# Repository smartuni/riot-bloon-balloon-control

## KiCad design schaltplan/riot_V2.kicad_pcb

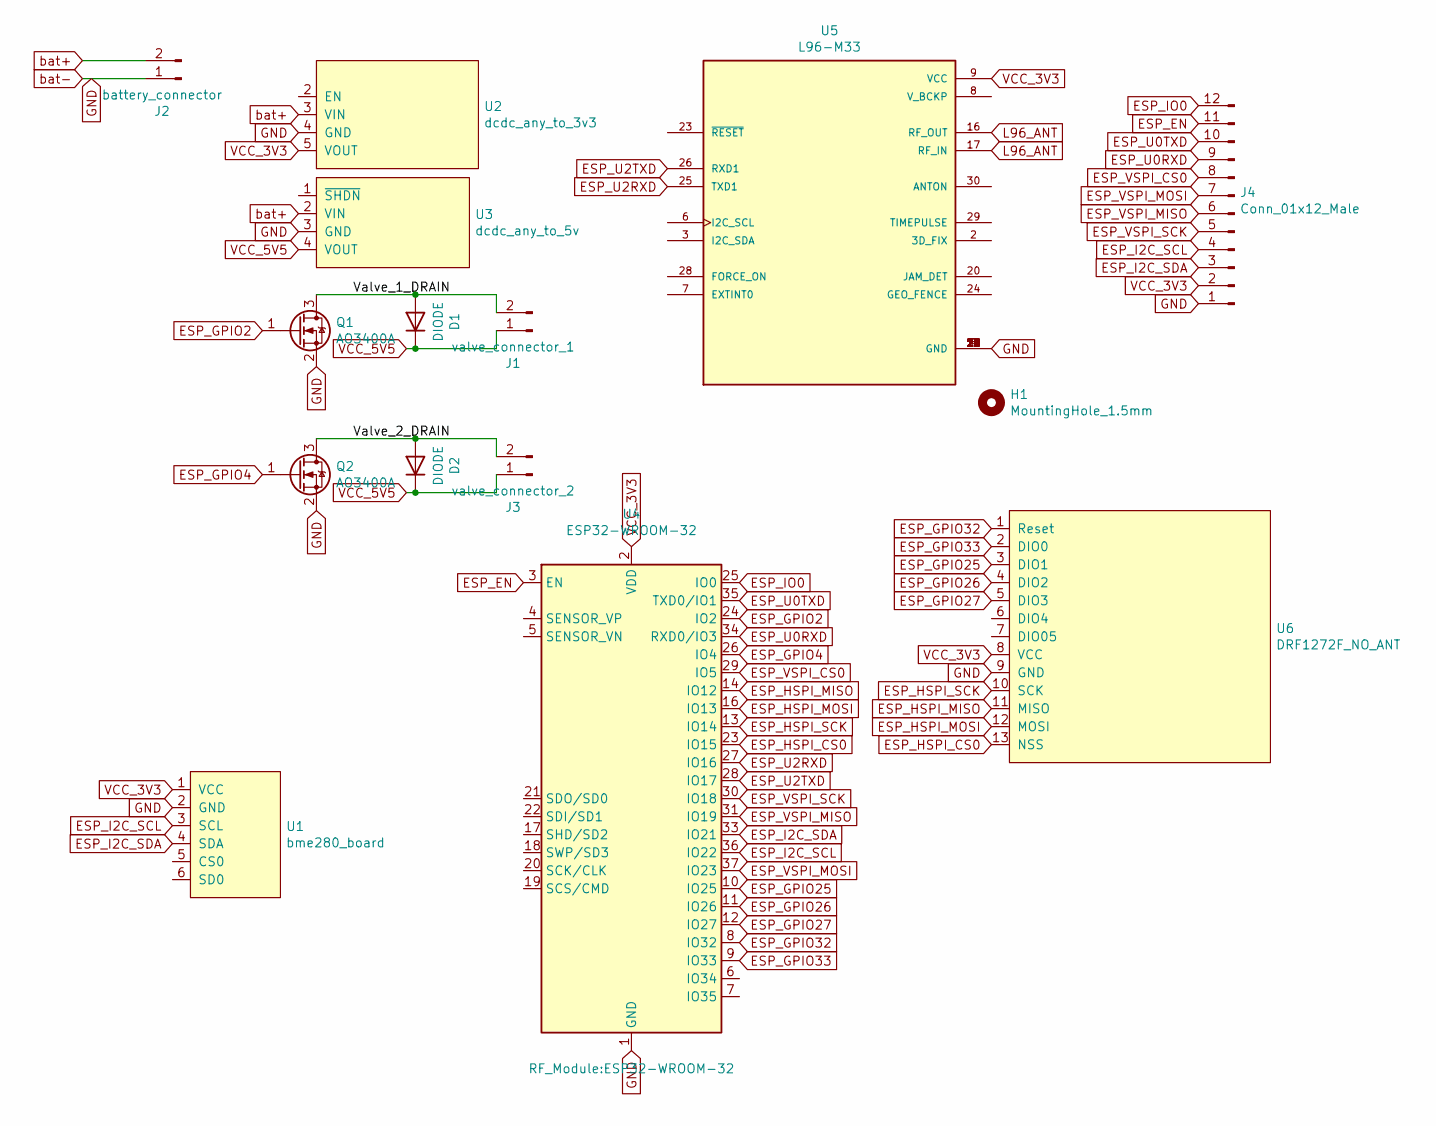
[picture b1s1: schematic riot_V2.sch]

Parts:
D1, D2: DIODE; D_A-405_P2.54mm_Vertical_AnodeUp
H1: MountingHole_1.5mm
J1: valve_connector_1; PinHeader_1x02_P2.54mm_Vertical
J2: battery_connector; PinHeader_1x02_P2.54mm_Vertical
J3: valve_connector_2; PinHeader_1x02_P2.54mm_Vertical
J4: Conn_01x12_Male; PinHeader_1x12_P2.54mm_Vertical
Q1, Q2: AO3400A; SOT-23
U1: bme280_board
U2: dcdc_any_to_3v3
U3: dcdc_any_to_5v
U4: ESP32-WROOM-32
U5: L96-M33; XCVR_L96-M33
U6: DRF1272F_NO_ANT

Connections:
/Valve_1_DRAIN: D1.1 (A), J1.2, Q1.3 (D)
/Valve_2_DRAIN: D2.1 (A), J3.2, Q2.3 (D)
ESP_EN: J4.11, U4.3 (EN)
ESP_GPIO2: Q1.1 (G), U4.24 (IO2)
ESP_GPIO4: Q2.1 (G), U4.26 (IO4)
ESP_GPIO25: U4.10 (IO25), U6.3 (DIO1)
ESP_GPIO26: U4.11 (IO26), U6.4 (DIO2)
ESP_GPIO27: U4.12 (IO27), U6.5 (DIO3)
ESP_GPIO32: U4.8 (IO32), U6.1 (Reset)
ESP_GPIO33: U4.9 (IO33), U6.2 (DIO0)
ESP_HSPI_CS0: U4.23 (IO15), U6.13 (NSS)
ESP_HSPI_MISO: U4.14 (IO12), U6.11 (MISO)
ESP_HSPI_MOSI: U4.16 (IO13), U6.12 (MOSI)
ESP_HSPI_SCK: U4.13 (IO14), U6.10 (SCK)
ESP_I2C_SCL: J4.4, U1.3 (SCL), U4.36 (IO22)
ESP_I2C_SDA: J4.3, U1.4 (SDA), U4.33 (IO21)
ESP_IO0: J4.12, U4.25 (IO0)
ESP_U0RXD: J4.9, U4.34 (RXD0/IO3)
ESP_U0TXD: J4.10, U4.35 (TXD0/IO1)
ESP_U2RXD: U4.27 (IO16), U5.25 (TXD1)
ESP_U2TXD: U4.28 (IO17), U5.26 (RXD1)
ESP_VSPI_CS0: J4.8, U4.29 (IO5)
ESP_VSPI_MISO: J4.6, U4.31 (IO19)
ESP_VSPI_MOSI: J4.7, U4.37 (IO23)
ESP_VSPI_SCK: J4.5, U4.30 (IO18)
GND: J2.1, J4.1, Q1.2 (S), Q2.2 (S), U1.2 (GND), U2.4 (GND), U3.3 (GND), U4.1 (GND), U4.15 (GND), U4.38 (GND), U4.39 (GND), U5.4 (GND), U5.5 (GND), U5.10 (GND), U5.11 (GND), U5.12 (GND), U5.13 (GND), U5.14 (GND), U5.15 (GND), U5.18 (GND), U5.19 (GND), U5.21 (GND), U5.22 (GND), U5.27 (GND), U5.31 (GND), U6.9 (GND)
L96_ANT: U5.16 (RF_OUT), U5.17 (RF_IN)
VCC_3V3: J4.2, U1.1 (VCC), U2.5 (VOUT), U4.2 (VDD), U5.9 (VCC), U6.8 (VCC)
VCC_5V5: D1.2 (K), D2.2 (K), J1.1, J3.1, U3.4 (VOUT)
bat+: J2.2, U2.3 (VIN), U3.2 (VIN)

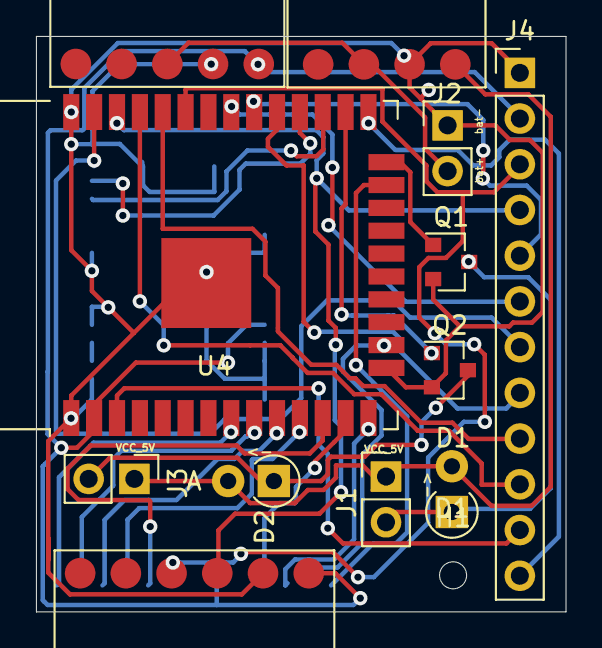
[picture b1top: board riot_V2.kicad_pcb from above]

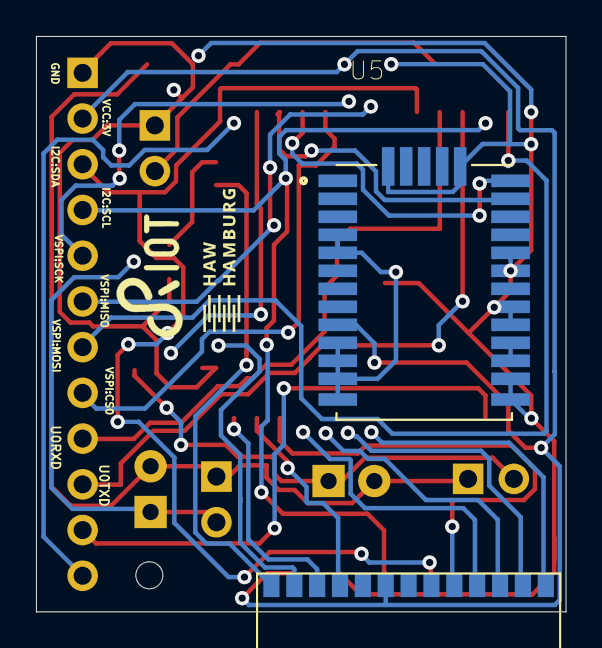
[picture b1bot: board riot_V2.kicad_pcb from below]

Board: 2 copper layers, 29.4 x 32.0 mm, 15 parts (2 on the bottom side), 30 nets.

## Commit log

2021-01-18 Add files
2021-01-18 Add RIOT submodule
2021-01-18 Fix makefile path
2021-01-18 Fix lora
2021-01-18 Fix closing shell when lora can not connect
2021-01-18 Fix bme280 address define
2021-01-18 Fix lora join else
2021-01-18 Fix lora datarate
2021-01-18 Fixed GPS (hopefully)
2021-01-18 fix print
2021-01-18 Add NMEA print
2021-01-18 Fix gps
2021-01-18 Inreased thread height
2021-01-18 increased height just a bit
2021-01-19 Finish gps etc.
2021-01-19 Add en and io0 pin to mini-loon board
2021-01-25 Interface for controlling LEDs
2021-01-25 LEDs finished, not tested
2021-01-25 Changed Number of LEDs to 2
2021-01-25 Add brightness define
2021-01-25 LED yellow in turn on, wait afer LoRa send to blink blue
2021-01-25 Change led brightness
2021-01-25 Update gitignore
2021-01-25 Debug LoRa send
2021-01-25 Finish led
2021-01-29 Renamed Mount Files
